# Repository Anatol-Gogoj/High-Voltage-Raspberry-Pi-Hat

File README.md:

# High Voltage Raspberry Pi Hat
A high voltage Raspberry Pi hat dedicated to controlling and powering Dielectric Elastomer Actuators (DEAs) through a dedicated circuit without the risk of burning out expensive high voltage equipment.

Two channels, up to 5 kV into loads under 1 nF, with independent charge, hold and active
discharge per channel and a passive 1 GOhm bleeder across each output. Rev B fits the standard
65 x 56 mm HAT outline with the HV section potted. KiCad 10 project in
[`HV Pi Hat/`](HV%20Pi%20Hat/); design decisions are in
[`HV Pi Hat/docs/adr/`](HV%20Pi%20Hat/docs/adr/).

**Safety:** this board generates 5 kV. It has not been fabricated or reviewed by a qualified
electrical engineer, and the HV spacing basis is still open (ADR-0003). Do not build or energize
it from this repository as it stands.

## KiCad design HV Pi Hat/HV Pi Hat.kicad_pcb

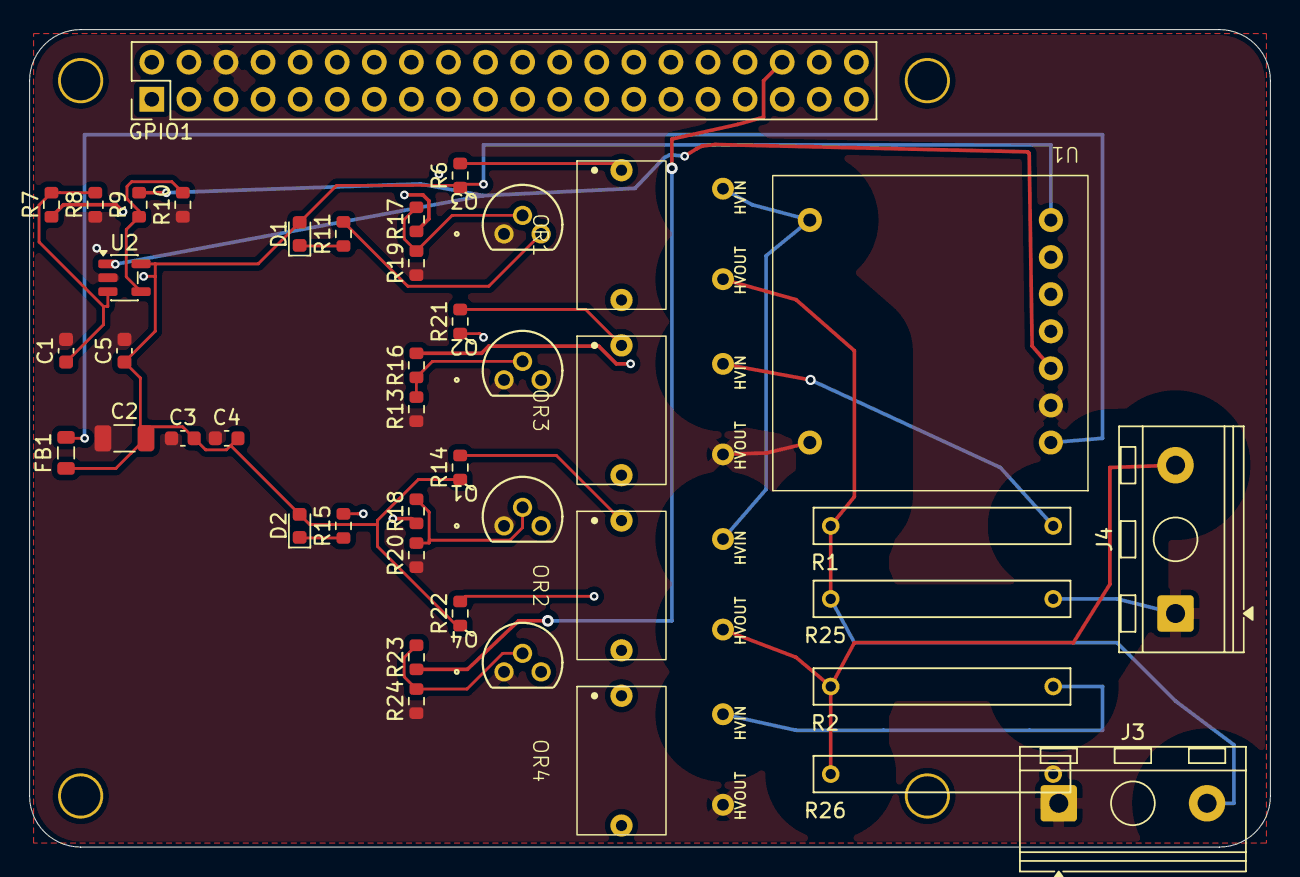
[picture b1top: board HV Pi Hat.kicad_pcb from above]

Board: 4 copper layers, 85.0 x 56.0 mm, 47 parts (0 on the bottom side), 30 nets.

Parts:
C1, C3: 1 uF; C_0603_1608Metric
C2: 47 uF; C_1206_3216Metric
C4, C5: 0.1 uF; C_0603_1608Metric
D1, D2: LED; LED_0603_1608Metric
FB1: FerriteBead; L_0805_2012Metric
GPIO1: PinHeader_2x20_P2.54mm_Vertical
H1, H2, H3, H4: MountingHole_2.7mm_M2.5_Pad_TopBottom
J3, J4: HV_Term_1x2; TerminalBlock_RND_205-00241_1x02_P10.16mm_Horizontal
OR1, OR2, OR3, OR4: HVM OR-100
Q1, Q2, Q3, Q4: TO-92_MC_MCH
R1, R2: 100 M; RESRR1524W50L1760T250H500
R6, R14, R21, R22: 51; R_0603_1608Metric
R7, R10, R13, R19, R20, R24: 10k; R_0603_1608Metric
R8: 100k; R_0603_1608Metric
R9: 5.6k; R_0603_1608Metric
R11, R15: 470; R_0603_1608Metric
R16, R17, R18, R23: 100; R_0603_1608Metric
R25, R26: 1G; RESRR1524W50L1760T250H500
U1: SMHV0550
U2: MCP6001-OT; SOT-23-5

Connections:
+5V: C2.2, C3.2, C4.2, C5.1, D1.2, D2.2, FB1.1, GPIO1.2, R6.1, R14.1, R21.1, R22.1, U1.7, U2.5
/CH1_CHG_DRN: OR1.1, Q3.3, R11.2
/CH1_CHG_GATE: Q3.2, R17.2, R19.2
/CH1_DIS_DRN: OR3.1, Q2.3
/CH1_DIS_GATE: Q2.2, R13.2, R16.1
/CH1_DIS_LED: OR3.2, R21.2
/CH2_CHG_DRN: OR2.1, Q1.3, R15.2
/CH2_CHG_GATE: Q1.2, R18.2, R20.2
/CH2_CHG_LED: OR2.2, R14.2
/CH2_DIS_DRN: OR4.1, Q4.3
/CH2_DIS_GATE: Q4.2, R23.2, R24.2
/CH2_DIS_LED: OR4.2, R22.2
/GPIO_5: GPIO1.29, R17.1
/GPIO_6: GPIO1.31, R16.2
/GPIO_12: GPIO1.32, R7.1
/GPIO_12_Boost: R9.2, U1.3, U2.1
/GPIO_16: GPIO1.36, R23.1
/GPIO_26: GPIO1.37, R18.1
/HV_CH1: J3.2, OR1.4, R1.1, R25.1
/HV_CH1_DIS: OR3.3, R1.2
/HV_CH2: J4.2, OR2.4, R2.1, R26.1
/HV_CH2_DIS: OR4.3, R2.2
/HV_RAIL: OR1.3, OR2.3, U1.8
/PGM_IN: C1.1, R7.2, R8.2, U2.3
GND: C1.2, C2.1, C3.1, C4.1, C5.2, GPIO1.6, J3.1, J4.1, OR3.4, OR4.4, Q1.1, Q2.1, Q3.1, Q4.1, R8.1, R10.1, R13.1, R19.1, R20.1, R24.1, R25.2, R26.2, U1.2, U1.9, U2.2
unnamed: D1.1, R11.1
unnamed: D2.1, R15.1
unnamed: OR1.2, R6.2
unnamed: FB1.2, U1.1
unnamed: R9.1, R10.2, U2.4

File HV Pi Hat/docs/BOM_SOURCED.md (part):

# Sourced Bill of Materials — 5 kV HV Raspberry Pi HAT (DEA driver)

**Date sourced:** 2026-06-07
**Distributors:** DigiKey preferred, Mouser/LCSC as fallback.
**Verification:** Specialty/high-risk parts (HVM modules, SHV connector, 1 GΩ HV resistor, TN0610 MOSFET) verified via live web lookups. Commodity passives use representative in-stock DigiKey catalog parts per value.

> **Pricing note:** DigiKey's product pages block automated reads (HTTP 403), so unit prices marked "~" were obtained from search snippets / mirror distributors and should be confirmed at checkout. Stock figures are approximate as of the date above.

---

## BOM Table

| Ref(s) | Qty | Value/Part | Package | Manufacturer + MPN | DigiKey/Mouser PN | In stock? (Y/N + approx qty) | Unit price | Notes |
|---|---|---|---|---|---|---|---|---|
| U1 | 1 | SMHV0550 — 5 kV / 200 µA programmable HV DC-DC | Module 0.85"x0.85"x0.6" | HVM Technology SMHV0550 | DigiKey **2244-SMHV0550-ND** (base), product 10708015 | Y — stocked catalog item ("ships today"); typically low/MOQ-of-1 qty, confirm at cart | ~$200–300 (confirm) | **Catalog item on DigiKey — no RFQ needed.** Output proportional to 0–5 V program input. 5 V ±10% supply. Also orderable direct from hvmtech.com (RFQ, tel 830-626-5552). The "-S2" suffix is a packaging/variant; the bare **SMHV0550** matches the schematic symbol. |
| OR1–OR4 | 4 | OPTO-100-05 — 10 kV HV opto-coupler | PCB pkg 0.55"L x 0.65"W x 0.25"H | HVM Technology OPTO-100-05 | DigiKey **2244-OPTO-100-05-ND**, product 16378579 | Y — stocked catalog item ("ships today") | ~$94.74 DK (≈$74 at LCSC C17566441) | **Catalog item on DigiKey — orderable, not RFQ-only.** 10 kV reverse-voltage rating, internal current-limit R, no external parts. LED Vf = 3.25 V @ 100 mA. **4 needed = ~$380 — largest BOM cost driver after U1.** |
| U2 | 1 | MCP6001 op-amp, 1 MHz RRIO | SOT-23-5 ("OT") | Microchip MCP6001T-I/OT | DigiKey **MCP6001T-I/OTCT-ND** (cut tape), product 551760 | Y — high stock (mainstream part) | ~$0.42 | "OT" = SOT-23-5 per schematic (symbol MCP6001-OT). I-grade (-40…+85 °C). |
| Q1–Q4 | 4 | N-MOSFET, 100 V, logic-level | TO-92 | Microchip (Supertex) TN0610N3-G | DigiKey **TN0610N3-G-ND**, product 4902374 | Y — **active, ships today** | ~$0.70 | 100 V Vds, 500 mA, Vgs(th) typ ~1.5 V (logic-level), 1 W. Confirmed NOT EOL. Schematic uses the **-P013** ammo/tape variant (DigiKey **TN0610N3-G-P013** / Mouser 579-TN0610N3-G-P013) — order whichever pack form you prefer; die is identical. See alternatives note below. |
| R1, R2 | 2 | 100 MΩ HV resistor, 1%, 7 kV | Axial 0317 (lead pitch 15.24 mm) | Murata MHR0317SA107F70 | DigiKey **MHR0317SA107F70-ND** (verify current DK#); confirmed catalog part | Y — ~4,155 (mirror); on DigiKey catalog | ~$1.10 (qty1), ~$0.37 @1k | 100 MΩ confirmed (107 = 100 MΩ). 0.8 W. Matches schematic symbol/footprint exactly. |
| R25, R26 | 2 | 1 GΩ HV resistor, 1%, 7 kV (populated by default as the fail-safe bleeder; DNP-able) | Axial 0317 (lead pitch 15.24 mm) | Murata MHR0317SA108F70 | DigiKey product **9950895** (DK# MHR0317SA108F70-ND) | **Partial** — real Murata catalog part with live DigiKey page; one mirror showed 0 stock, so **verify live stock before ordering** | ~$1.10 (qty1) | **CONFIRMED this 1 GΩ part exists** in the same 0317 series (108 = 1000 MΩ). 7 kV rated, 0.8 W. Populated by default (fail-safe bleed-down), so stock matters: verify before ordering. Fallback if DK out: Ohmite "Slim-Mox"/Vishay VR37 GΩ-range HV axials (≥5 kV), or Vishay VHV/RNX. |
| J3, J4 | 2 | 1x2 screw terminal, 10.16 mm pitch (pad 1 = GND/HV return, pad 2 = HV out) | THT, footprint `TerminalBlock_RND_205-00241_1x02_P10.16mm_Horizontal` | Recommended: Phoenix Contact MKDS 10 HV/ 2-ZB-10,16 (1709681), pitch-compatible | See `docs/HV_CONNECTOR_OPTIONS.md` | Not re-checked | ~$5 (per the connector study) | SHV-R was rejected (3.5 kV continuous rating). The connector study ranks a direct-soldered HV silicone lead first; that option is tied to the footprint question in `adr/0004-board-footprint.md`. |
| GPIO1 | 1 | 2x20 (40-pin) 2.54 mm female header | THT, dual row | Sullins PPTC202LFBN-RC | DigiKey **S6104-ND**, product 807240 | Y — high stock | ~$1.10 | Plain 2x20 female socket (non-stacking). For a stacking/extended HAT header use Samtec SSQ-120-03-T-D or Sullins PPPC202LFBN-RC (S7123-ND). |
| D1, D2 | 2 | LED indicator, ~2 V | 0603 | Würth 150060GS75000 (green) | DigiKey **732-4971-1-ND** | Y — very high stock | ~$0.12 | Any 0603 LED is fine; green Vf ~2.0 V. Pair with appropriate series R (see 470 Ω / 1 k). |
| FB1 | 1 | Ferrite bead, 600 Ω @ 100 MHz, ≥0.5 A | 0805 | Murata BLM21AG601SN1D | DigiKey **490-1054-1-ND**, product 584251 | Y — very high stock | ~$0.10 | 600 Ω @100 MHz, 600 mA. For higher current use BLM21SP601SH1D (2.3 A, power line). |
| C2 | 1 | 47 µF, ≥10 V, X5R/X7R MLCC | 1206 | Murata GRM31CR61A476KE15L (47 µF 10 V X5R) | DigiKey **490-5523-1-ND** | Y — high stock | ~$0.30 | 1206, 10 V X5R. For more margin use 16 V (GRM31CR61C476K). |
| C1, C3 | 2 | 1 µF, ≥16 V MLCC | 0603 | Murata GRM188R61E105KA12D (1 µF 25 V X5R) | DigiKey **490-5523-2-... / 490-1543-1-ND** | Y — very high stock | ~$0.10 | 0603, 25 V X5R (>16 V margin). |
| C4, C5 | 2 | 0.1 µF, ≥16 V MLCC | 0603 | Murata GRM188R71H104KA93D (0.1 µF 50 V X7R) | DigiKey **490-3553-1-ND** | Y — very high stock | ~$0.10 | 0603, 50 V X7R. |
| R6, R14, R21, R22 | 4 | 51 Ω, 1%, 0.1 W | 0603 | Yageo RC0603FR-0751RL | DigiKey **311-51.0HRCT-ND** | Y — very high stock | ~$0.10 | 0603 0.1 W ≥ the ~0.09 W load. |
| R11, R15 | 2 | 470 Ω, 1% | 0603 | Yageo RC0603FR-07470RL | DigiKey **311-470HRCT-ND** | Y — very high stock | ~$0.10 | LED series resistors (with D1/D2). |
| R16, R17, R18, R23 | 4 | 100 Ω, 1% | 0603 | Yageo RC0603FR-07100RL | DigiKey **311-100HRCT-ND** | Y — very high stock | ~$0.10 | |
| R7, R10, R13, R19, R20, R24 | 6 | 10 kΩ, 1% | 0603 | Yageo RC0603FR-0710KL | DigiKey **311-10.0KHRCT-ND** | Y — very high stock | ~$0.10 | |
| R8 | 1 | 100 kΩ, 1% | 0603 | Yageo RC0603FR-07100KL | DigiKey **311-100KHRCT-ND** | Y — very high stock | ~$0.10 | |
| R9 | 1 | 5.6 kΩ, 1% | 0603 | Yageo RC0603FR-075K6L | DigiKey **311-5.60KHRCT-ND** | Y — very high stock | ~$0.10 | |

---

## SOURCING RISKS (needs user attention)

1. **SHV connector (J3, J4) — RESOLVED 2026-06-07 → now a 1×2 screw terminal.**
   > **UPDATE:** J3/J4 are no longer SHV. Per the user decision they are now a generic **1×2 screw
   > terminal, 10.16 mm pitch** (`TerminalBlock_RND_205-00241`, pitch-compatible with **Phoenix MKDS
   > 10 HV / 1709681**); see the dedicated study `docs/HV_CONNECTOR_OPTIONS.md`. **Correction to the
   > note below:** the Radiall **R317580000 operating rating is ~3.5 kV** (its 12 kV is only mated-pair
   > *withstand*), so it does **not** solve the continuous-rating problem either; no board-mount SHV
   > jack exceeds 3.5 kV continuous. The genuinely-safe 5 kV options are panel-mount MHV/Radiall
   > (operating-rated) or a **direct-soldered HV silicone lead** (best). Original SHV note kept below.

1b. **(superseded) Original SHV note.**
   - The schematic footprint is named `4912-SHV-R-ND`, which mixes two unrelated parts: **Keystone 4912** is a 0.25" quick-fit *terminal* (not SHV), while **SHV-R** is the **Tyclon** SHV jack. The actual orderable SHV jack is **Tyclon SHV-R** (DigiKey marketplace 19092455, ~$12.08, ~929 in stock).
   - **Problem:** the Tyclon SHV line is rated **3.5 kV continuous, 5 kV withstand for 1 minute only.** Running it at 5 kV *continuous* gives essentially zero margin and is outside its continuous rating.
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
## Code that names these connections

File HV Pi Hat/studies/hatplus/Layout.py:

# Layout.py - candidate placement for the HAT+ outline study (board coordinates, mm).
# Footprint origin and rotation follow KiCad: rotation -90 maps local (x, y) to board (X - y, Y + x).

# HAT+ outline: 65 x 56.5 mm, left/top edges where rev A had them, 3 mm corners
Outline = (117.5, 86.0, 182.5, 142.5, 3.0)

# Pot (ADR-0003 interim): 3 mm beyond HV copper; notch radius around the H4 screw
PotMargin = 3.0
H4Notch = (179.0, 138.5, 3.5)

# Soldered HV lead pads (replace the J3/J4 screw terminals)
LeadPad = 2.6
LeadDrill = 1.3
LeadRefs = ("J3", "J4")
Leads = [
    ("J3", "HV_Leads_CH1", [("1", "GND", (162.0, 139.2)), ("2", "/HV_CH1", (178.2, 123.2))]),
    ("J4", "HV_Leads_CH2", [("1", "GND", (168.5, 139.2)), ("2", "/HV_CH2", (178.2, 129.0))]),
]

Place = {
    # Mechanical: standard HAT+ hole pattern and header (unchanged from rev A)
    "H1": (179.0, 89.5, 0), "H2": (121.0, 89.5, 0), "H3": (121.0, 138.5, 0), "H4": (179.0, 138.5, 0),
    "GPIO1": (125.875, 90.775, 90),
    # HV module: courtyard x 160.0..182.2, y 96.5..118.7; LV pins on the top row, HV pin 8 bottom-left
    "U1": (160.3, 96.8, -90),
    # Opto column: LED pins face left (x 147.05), HV pins face right (x 154.0)
    "OR1": (144.0, 95.8, -90),   # CH1 charge: pin3 HV_RAIL, pin4 HV_CH1
    "OR2": (144.0, 107.3, -90),  # CH2 charge: pin3 HV_RAIL, pin4 HV_CH2
    "OR3": (144.0, 118.8, -90),  # CH1 discharge: pin3 HV_CH1_DIS, pin4 GND
    "OR4": (144.0, 130.3, -90),  # CH2 discharge: pin3 HV_CH2_DIS, pin4 GND
    # HV resistors under U1, rotated 180 so pad1 (HV_CHx) is on the right
    "R1": (165.5, 121.0, 180),   # R_dis CH1: HV_CH1 / HV_CH1_DIS
    "R25": (165.5, 125.3, 180),  # R_safety CH1: HV_CH1 / GND
    "R26": (165.5, 129.6, 180),  # R_safety CH2: HV_CH2 / GND
    "R2": (165.5, 133.9, 180),   # R_dis CH2: HV_CH2 / HV_CH2_DIS
    # Ferrite next to U1 pin 1 (VIN); the +5V bulk caps sit at the power entry by header pins 2/4
    # (ADR-0001: bulk stays on +5V, before the ferrite)
    "FB1": (177.0, 94.6, 0),
    "C2": (121.0, 106.0, 90), "C3": (121.0, 110.0, 90), "C4": (121.0, 113.2, 90),
    # PGM stage, top-left
    "U2": (125.0, 97.5, 0), "R9": (128.5, 97.5, 90), "R10": (128.5, 100.8, 90), "C5": (128.0, 94.4, 0),
    "R7": (120.5, 98.0, 90), "R8": (120.5, 101.6, 90), "C1": (123.8, 101.4, 0),
}


def Cluster(Oy, Q, Rled, Rgate, Rpd, Rind=None, Led=None):
    # One opto driver, aligned with the opto whose origin y is Oy (LED+ at Oy+0.635, LED- at Oy+9.525)
    Place[Q] = (139.0, Oy + 9.5, 0)          # drain (pin 3) at x 141.54 faces the opto LED- pin
    Place[Rled] = (141.0, Oy + 1.2, 0)       # +5V to LED+
    Place[Rgate] = (134.5, Oy + 8.2, 0)      # GPIO to gate
    Place[Rpd] = (134.5, Oy + 10.5, 0)       # gate pulldown
    if Rind:
        Place[Led] = (136.0, Oy + 1.2, 0)    # indicator LED, anode on +5V
        Place[Rind] = (136.0, Oy + 4.0, 0)   # indicator resistor to the drain


Cluster(95.8, "Q3", "R6", "R17", "R19", "R11", "D1")    # OR1, GPIO_5
Cluster(107.3, "Q1", "R14", "R18", "R20", "R15", "D2")  # OR2, GPIO_26
Cluster(118.8, "Q2", "R21", "R16", "R13")               # OR3, GPIO_6
Cluster(130.3, "Q4", "R22", "R23", "R24")               # OR4, GPIO_16

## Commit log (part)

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2025-12-08 Enhance README description for safety clarification
    Expanded description to include safety information regarding high voltage equipment.
2025-12-08 Add LICENSE file
2026-06-05 pre-control-rework
